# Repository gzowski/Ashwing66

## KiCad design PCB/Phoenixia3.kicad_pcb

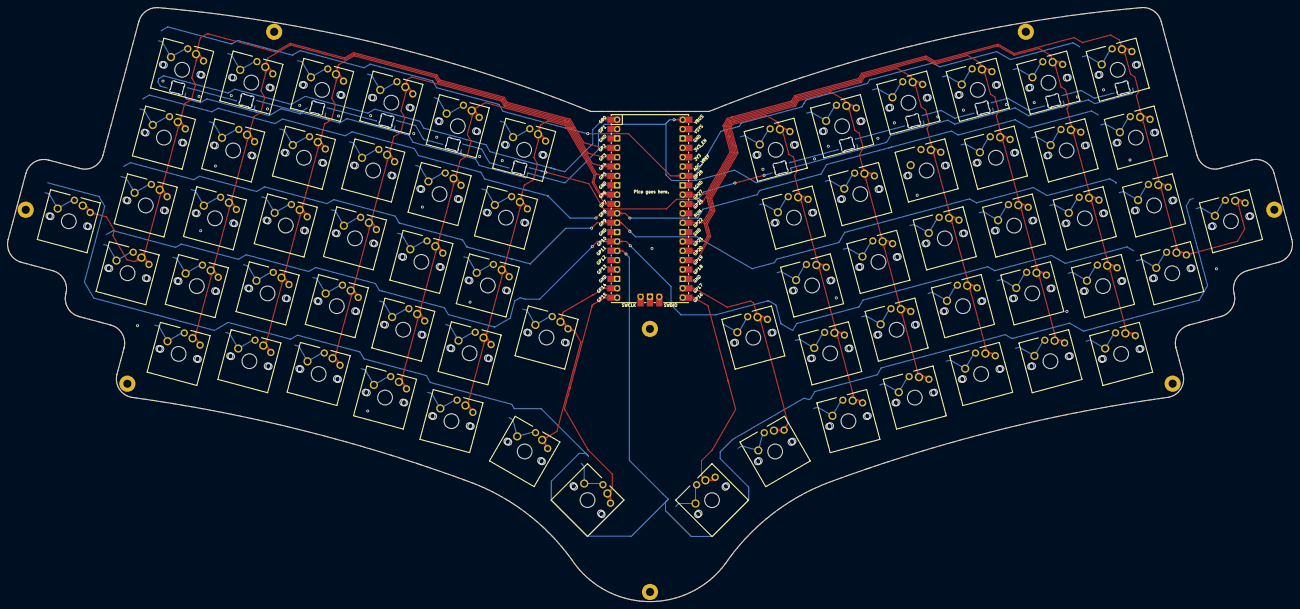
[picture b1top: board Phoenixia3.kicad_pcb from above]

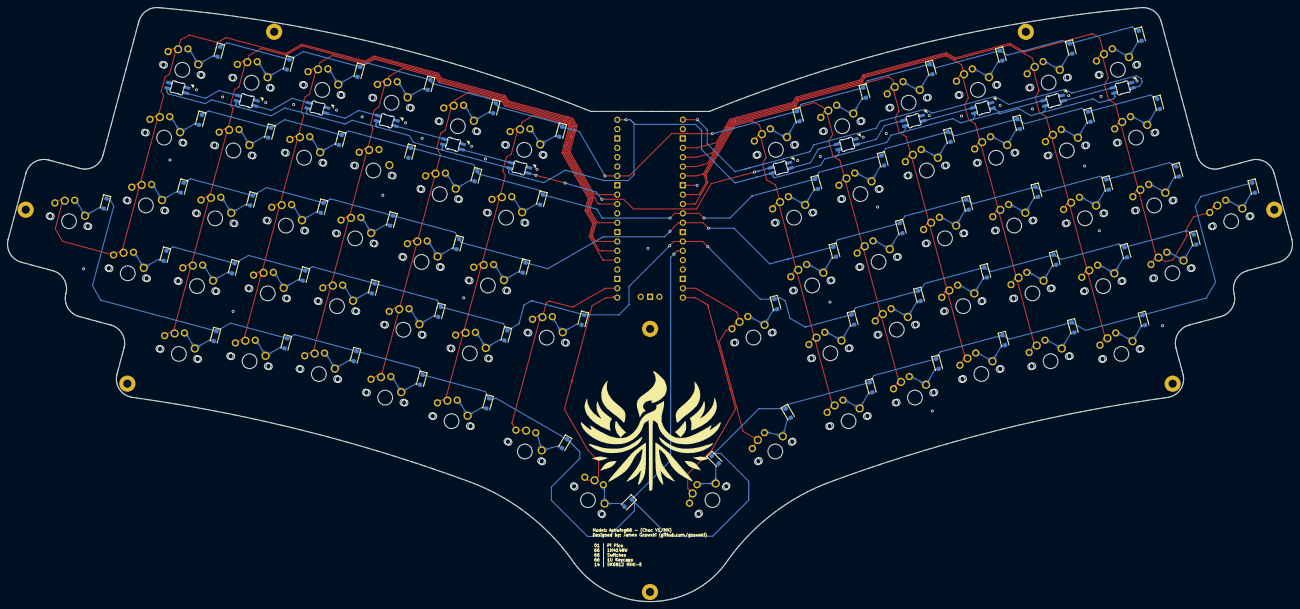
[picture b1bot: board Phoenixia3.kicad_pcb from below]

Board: 2 copper layers, 348.6 x 161.2 mm, 140 parts (69 on the bottom side), 99 nets.

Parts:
D0, D1, D2, D3, D4, D5, D6, D7, D8, D9, D10, D11, D16, D17, D18, D19, D20, D21, D22, D23, D24, D25, D26, D27, D32, D32#2, D32#3, D33, D34, D35, D36, D37, D38, D39, D40, D41, D42, D43, D44, D44#2, D48, D49, D50, D51, D52, D53, D54, D55, D56, D57, D58, D59, D64, D65, D66, D67, D68, D69, D69#2, D70, D70#2, D71, D72, D73, D74, D75: D; D_SOD-123F_2
H4, H4#2, H4#3, H4#4, H4#5, H4#6, H4#7: MountingHole; MountingHole_2.2mm_M2_Pad
K0: Blank; SW_Cherry_Choc5_MX_1.00u_PCB_LED
K1, K2, K3, K4, K5, K6, K7, K8, K9, K10, K11: Blank; SW_Cherry_Choc5_MX_1.00u_PCB_LED_3D2
K16: Blank; SW_Cherry_Choc5_MX_1.00u_PCB
K17, K18, K19, K20, K21, K22, K23, K24, K25, K26, K27, K32, K33, K34, K35, K36, K37, K38, K39, K40, K41, K42, K43, K44, K44#2, K48, K49, K50, K51, K52, K53, K54, K55, K56, K57, K58, K59, K60, K60#2, K64, K65, K66, K67, K68, K69, K69#2, K70, K70#2, K71, K72, K73, K74, K75: Blank; SW_Cherry_Choc5_MX_1.00u_PCB_3D
pico: RPi_Pico_SMD_TH

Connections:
Col_0: K0.1, K16.1, K32.1, K48.1, K60#2.1, pico.4
Col_1: K1.1, K17.1, K33.1, K49.1, K64.1, pico.5
Col_2: K2.1, K18.1, K34.1, K50.1, K65.1, pico.6
Col_3: K3.1, K19.1, K35.1, K51.1, K66.1, pico.7
Col_4: K4.1, K20.1, K36.1, K52.1, K67.1, pico.9
Col_5: K5.1, K21.1, K37.1, K53.1, K68.1, pico.10
Col_6: K60.1, K69#2.1, pico.19
Col_7: K69.1, pico.20
Col_8: K70.1, pico.21
Col_9: K44.1, K70#2.1, pico.22
Col_10: K6.1, K22.1, K38.1, K54.1, K71.1, pico.25
Col_11: K7.1, K23.1, K39.1, K55.1, K72.1, pico.26
Col_12: K8.1, K24.1, K40.1, K56.1, K73.1, pico.27
Col_13: K9.1, K25.1, K41.1, K57.1, K74.1, pico.29
Col_14: K10.1, K26.1, K42.1, K58.1, K75.1, pico.31
Col_15: K11.1, K27.1, K43.1, K44#2.1, K59.1, pico.32
GND: K0.3, K1.3, K2.3, K3.3, K4.3, K5.3, K6.3, K7.3, K8.3, K9.3, K10.3, K11.3, pico.3, pico.8, pico.13, pico.18, pico.23, pico.28, pico.33, pico.38
LED1: K0.4, pico.1
LED2: K0.2, K1.4
LED3: K1.2, K2.4
LED4: K2.2, K3.4
LED5: K3.2, K4.4
LED6: K4.2, K5.4
LED7: K5.2, K6.4
LED8: K6.2, K7.4
LED9: K7.2, K8.4
LED10: K8.2, K9.4
LED11: K9.2, K10.4
LED12: K10.2, K11.4
NET-(DEXT-A): D69#2.2 (A), K69.2
unnamed: D0.2 (A), K0.2
unnamed: D1.2 (A), K1.2
unnamed: D2.2 (A), K2.2
unnamed: D3.2 (A), K3.2
unnamed: D4.2 (A), K4.2
unnamed: D5.2 (A), K5.2
unnamed: D6.2 (A), K6.2
unnamed: D7.2 (A), K7.2
unnamed: D8.2 (A), K8.2
unnamed: D9.2 (A), K9.2
unnamed: D10.2 (A), K10.2
unnamed: D11.2 (A), K11.2
unnamed: D16.2 (A), K16.2
unnamed: D17.2 (A), K17.2
unnamed: D18.2 (A), K18.2
unnamed: D19.2 (A), K19.2
unnamed: D20.2 (A), K20.2
unnamed: D21.2 (A), K21.2
unnamed: D22.2 (A), K22.2
unnamed: D23.2 (A), K23.2
unnamed: D24.2 (A), K24.2
unnamed: D25.2 (A), K25.2
unnamed: D26.2 (A), K26.2
unnamed: D27.2 (A), K27.2
unnamed: D32#3.2 (A), K32.2
unnamed: D33.2 (A), K33.2
unnamed: D34.2 (A), K34.2
unnamed: D35.2 (A), K35.2
unnamed: D36.2 (A), K36.2
unnamed: D37.2 (A), K37.2
unnamed: D38.2 (A), K38.2
unnamed: D39.2 (A), K39.2
unnamed: D40.2 (A), K40.2
unnamed: D41.2 (A), K41.2
unnamed: D42.2 (A), K42.2
unnamed: D43.2 (A), K43.2
unnamed: D44.2 (A), D44#2.2 (A), K44.2, K44#2.2
unnamed: D48.2 (A), K48.2
unnamed: D49.2 (A), K49.2
unnamed: D50.2 (A), K50.2
unnamed: D51.2 (A), K51.2
unnamed: D52.2 (A), K52.2
unnamed: D53.2 (A), K53.2
unnamed: D54.2 (A), K54.2
unnamed: D55.2 (A), K55.2
unnamed: D56.2 (A), K56.2
unnamed: D57.2 (A), K57.2
unnamed: D58.2 (A), K58.2
unnamed: D59.2 (A), K59.2
unnamed: D32.2 (A), D32#2.2 (A), K60.2, K60#2.2
unnamed: D70#2.2 (A), K70.2
unnamed: D64.2 (A), K64.2
unnamed: D65.2 (A), K65.2
unnamed: D66.2 (A), K66.2
unnamed: D67.2 (A), K67.2
unnamed: D68.2 (A), K68.2
unnamed: D69.2 (A), K69#2.2
unnamed: D70.2 (A), K70#2.2
unnamed: D71.2 (A), K71.2
unnamed: D72.2 (A), K72.2
unnamed: D73.2 (A), K73.2
unnamed: D74.2 (A), K74.2
unnamed: D75.2 (A), K75.2
Row_0: D0.1 (K), D1.1 (K), D2.1 (K), D3.1 (K), D4.1 (K), D5.1 (K), D6.1 (K), D7.1 (K), D8.1 (K), D9.1 (K), D10.1 (K), D11.1 (K), pico.34
Row_1: D16.1 (K), D17.1 (K), D18.1 (K), D19.1 (K), D20.1 (K), D21.1 (K), D22.1 (K), D23.1 (K), D24.1 (K), D25.1 (K), D26.1 (K), D27.1 (K), pico.11
Row_2: D32#3.1 (K), D33.1 (K), D34.1 (K), D35.1 (K), D36.1 (K), D37.1 (K), D38.1 (K), D39.1 (K), D40.1 (K), D41.1 (K), D42.1 (K), D43.1 (K), pico.12
Row_3: D32#2.1 (K), D44.1 (K), D48.1 (K), D49.1 (K), D50.1 (K), D51.1 (K), D52.1 (K), D53.1 (K), D54.1 (K), D55.1 (K), D56.1 (K), D57.1 (K), D58.1 (K), D59.1 (K), pico.14
Row_4: D32.1 (K), D44#2.1 (K), D64.1 (K), D65.1 (K), D66.1 (K), D67.1 (K), D68.1 (K), D69.1 (K), D69#2.1 (K), D70.1 (K), D70#2.1 (K), D71.1 (K), D72.1 (K), D73.1 (K), D74.1 (K), D75.1 (K), pico.15
VBUS: K1.1, K2.1, K3.1, K4.1, K5.1, K6.1, K7.1, K8.1, K9.1, K10.1, K11.1, pico.40
